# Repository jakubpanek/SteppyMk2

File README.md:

# Steppy Mk2

The goal of this project is to create a versatile robotic platform for robotic competitions.

It started with a very primitive PCB design that featured just a few, mostly through-hole components and evolved into a much more complicated design with over a hundred SMD components.

## Main features:
- NXP's FRDM dev boards, Arduino compatibility
- Two NEMA8 stepper motors
- Fits onto 100x100mm PCB for cheap manufacturing
- RGB LEDs
- OLED display
- Joystick
- Buzzer
- I²C battery voltage sensor
- Interchangeable sensor board

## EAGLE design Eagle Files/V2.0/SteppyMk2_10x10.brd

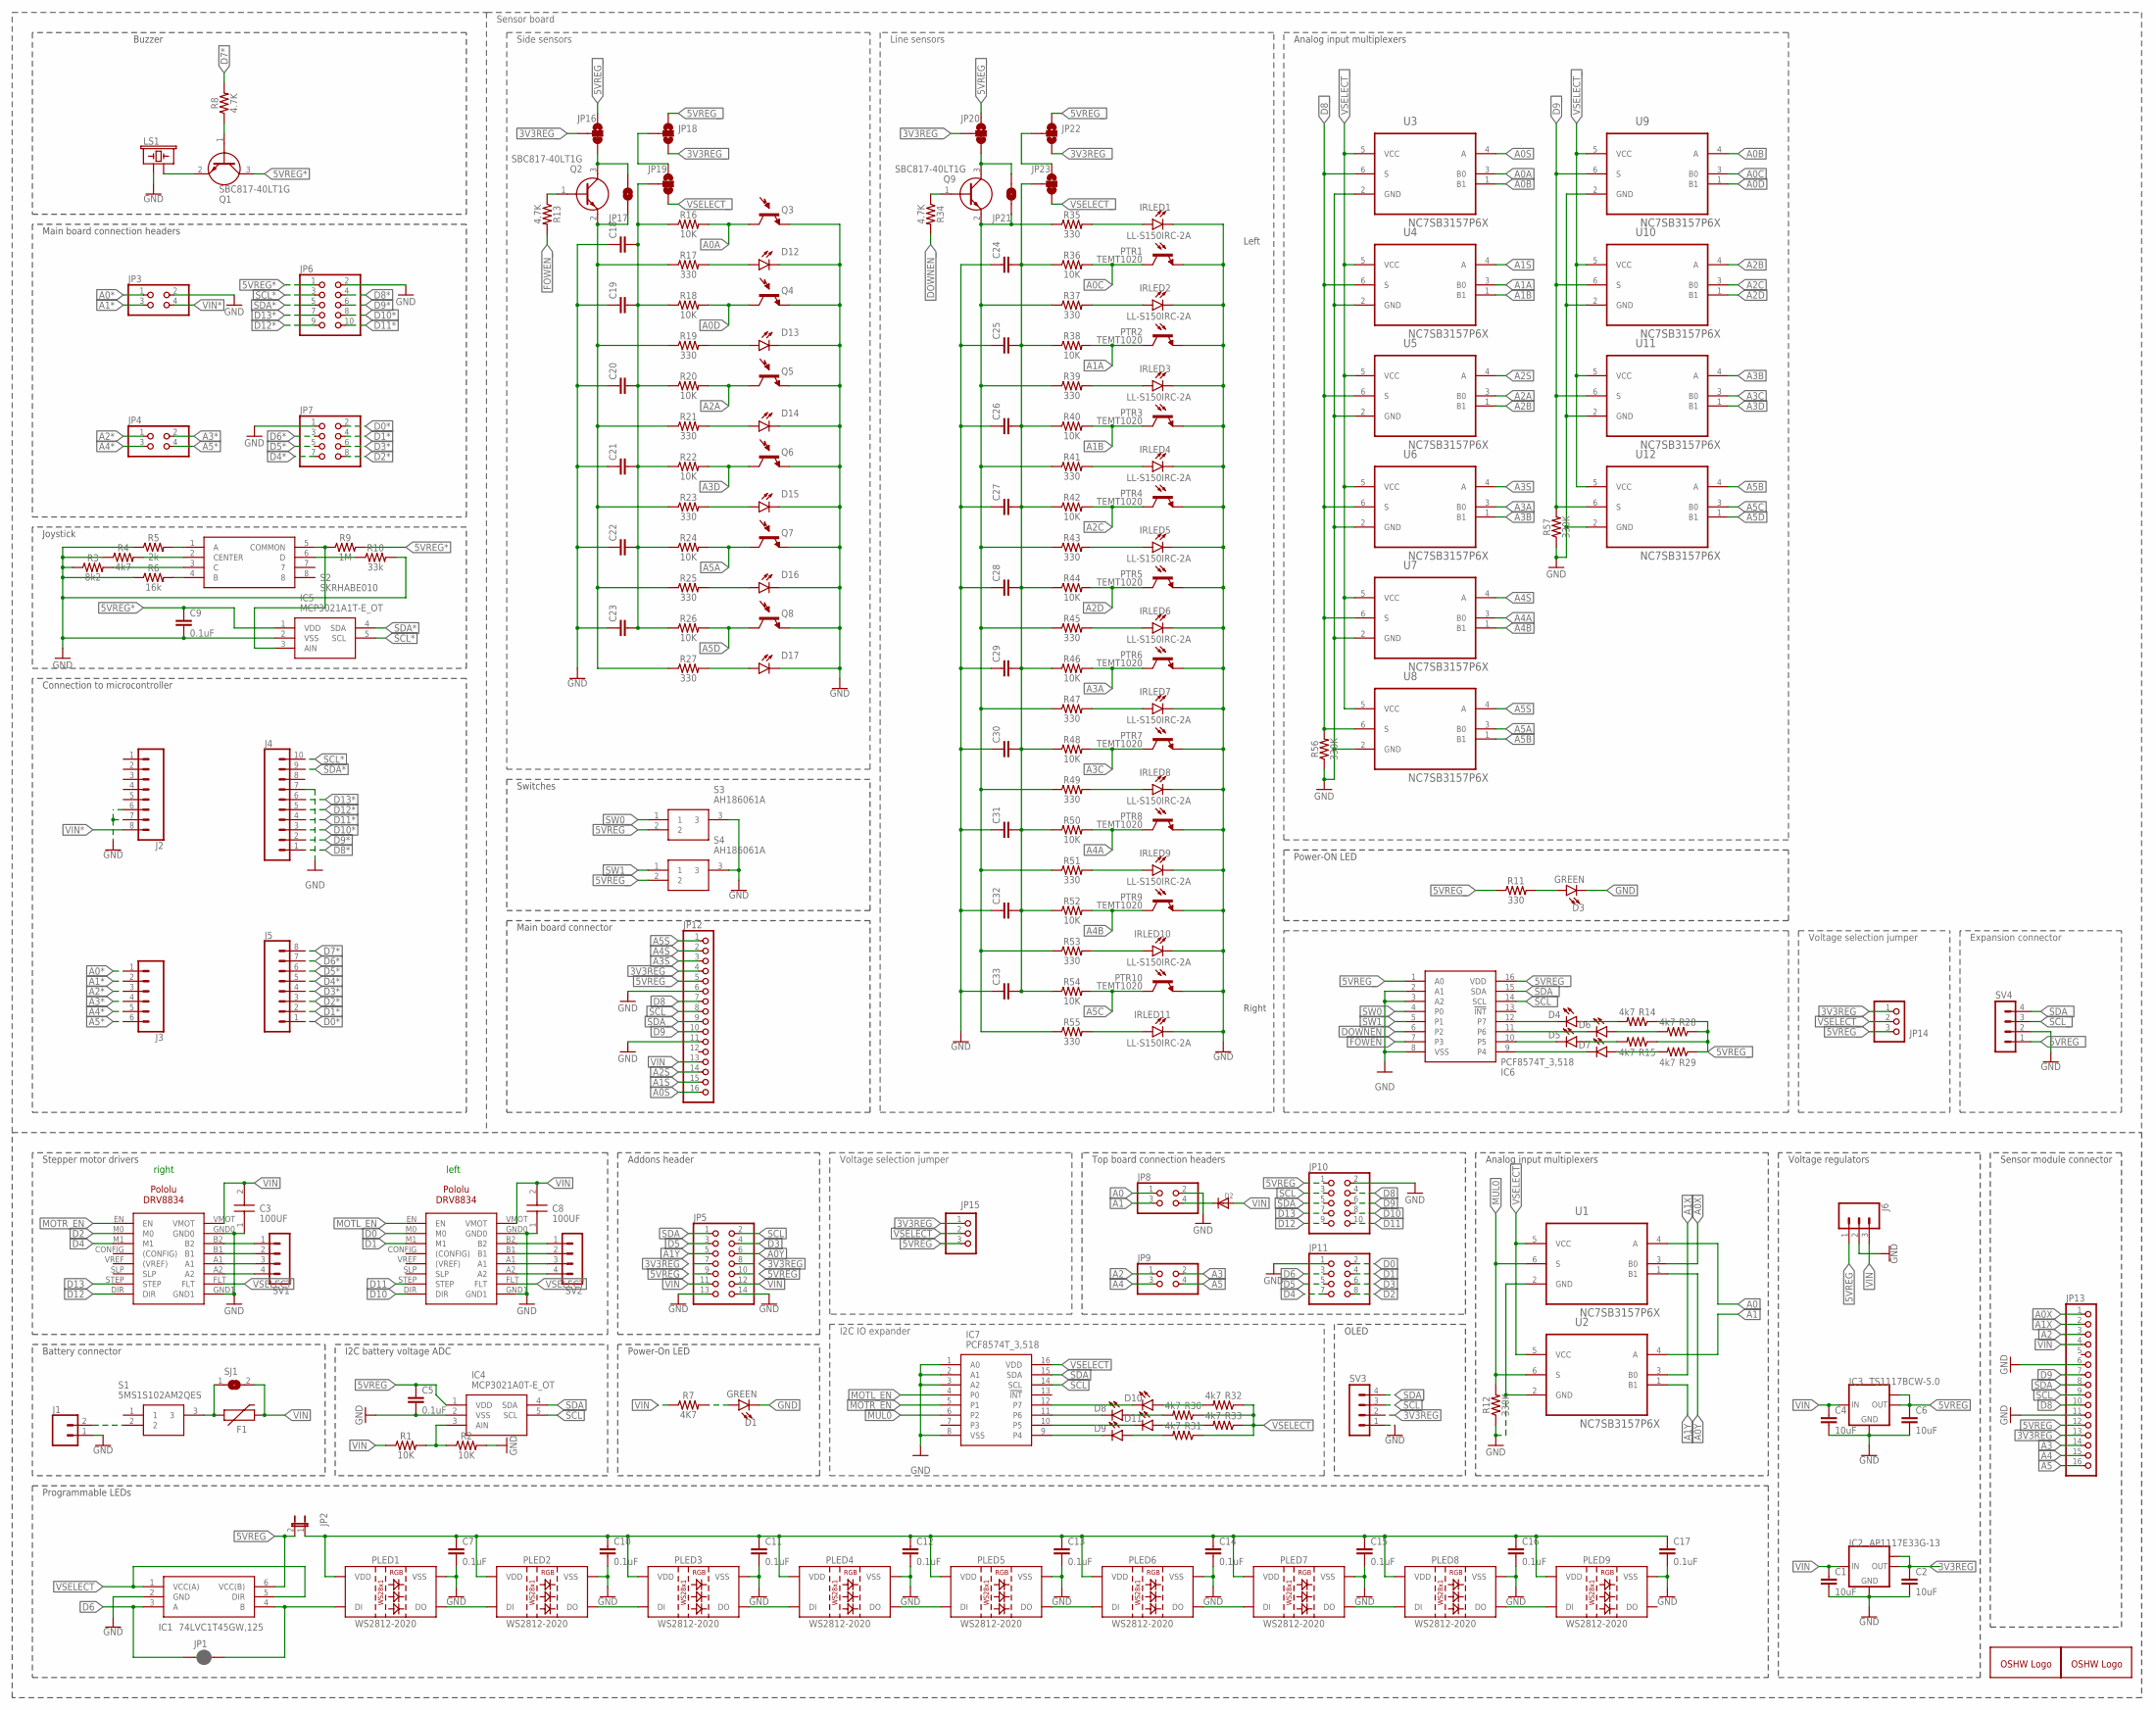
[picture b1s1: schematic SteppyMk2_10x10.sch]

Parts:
C1, C2, C4, C6: 10uF; 0805
C3, C8: 100UF; CAPM7058X610N
C5: 0.1uF; 0603
C7, C9, C10, C11, C12, C13, C14, C15, C16, C17: 0.1uF; C0805
C18, C19, C20, C21, C22, C23, C24, C25, C26, C27, C28, C29, C30, C31, C32, C33: C-EUC0805; C0805
D1, D3, D4, D5, D6, D7, D8, D9, D10, D11: GREEN; LED-1206
D2: DIODESMA; SMADIODE
D12, D13, D14, D15, D16, D17: LED-IRSIDE_EMITTER; LTE-302
DRV1, DRV2: POLOLU-DRV8825
F1: PPTC_PTH; PTH
GOLD_ORB_SM1: OSHWLOGOLOGO8MM; OSHW_8MM
GOLD_ORB_SM2: OSHWLOGOLOGO5MM; OSHW_5MM
IC1: 74LVC1T45GW,125; SOT65P210X110-6N
IC2: AP1117E33G-13; SOT223
IC3: TS1117BCW-5.0; SOT223
IC4: MCP3021A0T-E_OT; SOT95P280X145-5N
IC5: MCP3021A1T-E_OT; SOT95P280X145-5N
IC6, IC7: PCF8574T_3,518; SOIC127P1032X265-16N
IRLED1, IRLED2, IRLED3, IRLED4, IRLED5, IRLED6, IRLED7, IRLED8, IRLED9, IRLED10, IRLED11: LL-S150IRC-2A; LEDC3215X130N
J1: CONN_02; 1X02
J2, J5: CONN_08"; 1X08
J3: CONN_06SILK_FEMALE_PTH; 1X06
J4: CONN_10"; 1X10
J6: 455-1750-1-ND; 1X03
JP1: JUMPER-SMT_2_NC_PASTE_SILK; SMT-JUMPER_2_NC_PASTE_SILK
JP2: JP1E; JP1
JP3, JP4, JP8, JP9: PINHD-2X2; 2X02
JP5: PINHD-2X7; 2X07
JP6, JP10: PINHD-2X5; 2X05
JP7, JP11: PINHD-2X4; 2X04
JP12: PINHD-1X16/90; 1X16/90
JP13: PINHD-1X16; 1X16
JP14, JP15: PINHD-1X3; 1X03
JP16, JP19, JP20, JP23: JUMPER-SMT_3_1-NC_TRACE_NO-SILK; SMT-JUMPER_3_1-NC_TRACE_NO-SILK
JP17, JP21: JUMPER-SMT_2_NO_NO-SILK; SMT-JUMPER_2_NO_NO-SILK
JP18, JP22: JUMPER-SMT_3_NO_NO_SILK; SMT-JUMPER_3_0-NO_TRACE_NO-SILK
LS1: BUZZER-PTH_NO_SILK; BUZZER-12MM-NS
PLED1, PLED2, PLED3, PLED4, PLED5, PLED6, PLED7, PLED8, PLED9: WS2812-2020
PTR1, PTR2, PTR3, PTR4, PTR5, PTR6, PTR7, PTR8, PTR9, PTR10: TEMT1020
Q1, Q2, Q9: SBC817-40LT1G; SOT96P237X111-3N
Q3, Q4, Q5, Q6, Q7, Q8: LTR-301
R1, R2, R16, R18, R20, R22, R24, R26, R36, R38, R40, R42, R44, R46, R48, R50, R52, R54: 10K; 0805
R3: 8k2; 0805
R4, R14, R15, R28, R29, R30, R31, R32, R33: 4k7; 0805
R5: 2k; 0805
R6: 16k; 0805
R7: 4K7; 0805
R8, R13, R34: 4.7K; 0805
R9: 1M; 0805
R10: 33k; 0805
R11, R17, R19, R21, R23, R25, R27, R35, R37, R39, R41, R43, R45, R47, R49, R51, R53, R55: 330; 0805
R12, R56, R57: 330K; 0805
S1: 5MS1S102AM2QES
S2: SKRHABE010
S3, S4: AH186061A
SJ1: SJW
SV1, SV2, SV3, SV4: MA04-1
U1, U2, U3, U4, U5, U6, U7, U8, U9, U10, U11, U12: NC7SB3157P6X; SOT65P210X110-6N

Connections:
3V3REG: C2.1, IC2.2 (OUT), IC2.TAB (OUT1), JP5.7, JP5.8, JP13.13, JP15.1, SV3.2
3V3REG_: JP12.4, JP14.1, JP16.2, JP18.3, JP20.2, JP22.3
5VREG: C5.1, C6.1, IC1.6 (VCC(B)), IC3.2 (OUT), IC3.TAB (OUT1), IC4.1 (VDD), J6.1, JP2.2, JP5.9, JP5.10, JP10.1, JP13.12, JP15.3
5VREG*: C9.1, IC5.1 (VDD), JP6.1, Q1.3 (C), R9.2
5VREG_: IC6.1 (A0), IC6.16 (VDD), JP12.5, JP14.3, JP16.1, JP18.1, JP20.1, JP22.1, R11.1, R14.1, R15.1, R28.1, R29.1, S3.2, S4.2, SV4.1
A0: JP8.1, U1.4 (A)
A0*: J3.1, JP3.1
A0A: Q3.C (C1), R16.2, U3.3 (B0)
A0B: U3.1 (B1), U9.4 (A)
A0C: PTR1.1 (C), R36.2, U9.3 (B0)
A0D: Q4.C (C1), R18.2, U9.1 (B1)
A0S: JP12.16, U3.4 (A)
A0X: JP13.1, U1.3 (B0)
A0Y: JP5.6, U1.1 (B1)
A1: JP8.3, U2.4 (A)
A1*: J3.2, JP3.3
A1A: PTR2.1 (C), R38.2, U4.3 (B0)
A1B: PTR3.1 (C), R40.2, U4.1 (B1)
A1S: JP12.15, U4.4 (A)
A1X: JP13.2, U2.3 (B0)
A1Y: JP5.5, U2.1 (B1)
A2: JP9.1, JP13.3
A2*: J3.3, JP4.1
A2A: Q5.C (C1), R20.2, U5.3 (B0)
A2B: U5.1 (B1), U10.4 (A)
A2C: PTR4.1 (C), R42.2, U10.3 (B0)
A2D: PTR5.1 (C), R44.2, U10.1 (B1)
A2S: JP12.14, U5.4 (A)
A3: JP9.2, JP13.14
A3*: J3.4, JP4.2
A3A: PTR6.1 (C), R46.2, U6.3 (B0)
A3B: U6.1 (B1), U11.4 (A)
A3C: PTR7.1 (C), R48.2, U11.3 (B0)
A3D: Q6.C (C1), R22.2, U11.1 (B1)
A3S: JP12.3, U6.4 (A)
A4: JP9.3, JP13.15
A4*: J3.5, JP4.3
A4A: PTR8.1 (C), R50.2, U7.3 (B0)
A4B: PTR9.1 (C), R52.2, U7.1 (B1)
A4S: JP12.2, U7.4 (A)
A5: JP9.4, JP13.16
A5*: J3.6, JP4.4
A5A: Q7.C (C1), R24.2, U8.3 (B0)
A5B: U8.1 (B1), U12.4 (A)
A5C: PTR10.1 (C), R54.2, U12.3 (B0)
A5D: Q8.C (C1), R26.2, U12.1 (B1)
A5S: JP12.1, U8.4 (A)
D0: DRV2.M0, JP11.2
D0*: J5.1, JP7.2
D1: DRV2.M1, JP11.4
D1*: J5.2, JP7.4
D2: DRV1.M0, JP11.8
D2*: J5.3, JP7.8
D3: JP5.4, JP11.6
D3*: J5.4, JP7.6
D4: DRV1.M1, JP11.7
D4*: J5.5, JP7.7
D5: JP5.3, JP11.5
D5*: J5.6, JP7.5
D6: IC1.3 (A), JP1.1, JP11.3
D6*: J5.7, JP7.3
D7*: J5.8, R8.2
D8: JP10.4, JP13.10
D8*: J4.1, JP6.4
D8_: JP12.7, R56.2, U3.6 (S), U4.6 (S), U5.6 (S), U6.6 (S), U7.6 (S), U8.6 (S)
D9: JP10.6, JP13.7
D9*: J4.2, JP6.6
D9_: JP12.10, R57.2, U9.6 (S), U10.6 (S), U11.6 (S), U12.6 (S)
D10: DRV2.DIR, JP10.8
D10*: J4.3, JP6.8
D11: DRV2.STEP, JP10.10
D11*: J4.4, JP6.10
D12: DRV1.DIR, JP10.9
D12*: J4.5, JP6.9
D13: DRV1.STEP, JP10.7
D13*: J4.6, JP6.7
DOWNEN_: IC6.6 (P2), R34.2
FOWEN_: IC6.7 (P3), R13.2
GND: C1.2, C2.2, C3.1, C4.2, C5.2, C6.2, C7.2, C8.1, C9.2, C10.2, C11.2, C12.2, C13.2, C14.2, C15.2, C16.2, C17.2, C18.1, C19.1, C20.1, C21.1, C22.1, C23.1, C24.1, C25.1, C26.1, C27.1, C28.1, C29.1, C30.1, C31.1, C32.1, C33.1, D1.C, D3.C, D12.C, D13.C, D14.C, D15.C, D16.C, D17.C, DRV1.GND0, DRV1.GND1, DRV2.GND0, DRV2.GND1, IC1.2 (GND), IC2.1 (GND), IC3.1 (GND), IC4.2 (VSS), IC5.2 (VSS), IC6.2 (A1), IC6.3 (A2), IC6.8 (VSS), IC7.1 (A0), IC7.2 (A1), IC7.3 (A2), IC7.8 (VSS), IRLED1.2 (C), IRLED2.2 (C), IRLED3.2 (C), IRLED4.2 (C), IRLED5.2 (C), IRLED6.2 (C), IRLED7.2 (C), IRLED8.2 (C), IRLED9.2 (C), IRLED10.2 (C), IRLED11.2 (C), J1.1, J2.6, J2.7, J4.7, J6.2, JP3.2, JP5.13, JP5.14, JP6.2, JP7.1, JP8.2, JP10.2, JP11.1, JP12.6, JP12.11, JP13.6, JP13.11, LS1.+ (1), PLED1.2 (VSS), PLED2.2 (VSS), PLED3.2 (VSS), PLED4.2 (VSS), PLED5.2 (VSS), PLED6.2 (VSS), PLED7.2 (VSS), PLED8.2 (VSS), PLED9.2 (VSS), PTR1.2 (E), PTR2.2 (E), PTR3.2 (E), PTR4.2 (E), PTR5.2 (E), PTR6.2 (E), PTR7.2 (E), PTR8.2 (E), PTR9.2 (E), PTR10.2 (E), Q3.E (E1), Q4.E (E1), Q5.E (E1), Q6.E (E1), Q7.E (E1), Q8.E (E1), R2.2, R3.1, R4.1, R5.1, R6.1, R10.2, R12.1, R56.1, R57.1, S3.3, S4.3, SV3.1, SV4.2, U1.2 (GND), U2.2 (GND), U3.2 (GND), U4.2 (GND), U5.2 (GND), U6.2 (GND), U7.2 (GND), U8.2 (GND), U9.2 (GND), U10.2 (GND), U11.2 (GND), U12.2 (GND)
GND1: D6.C, IC6.11 (P6)
GND2: D5.C, IC6.10 (P5)
GND3: D7.C, IC6.9 (P4)
MOTL_EN: DRV2.EN, IC7.4 (P0)
MOTR_EN: DRV1.EN, IC7.5 (P1)
MUL0: IC7.6 (P2), R12.2, U1.6 (S), U2.6 (S)
unnamed: IRLED9.1 (A), R51.2
unnamed: IRLED2.1 (A), R37.2
unnamed: D4.A, R14.2
unnamed: D2.C, JP8.4
unnamed: Q2.1 (B), R13.1
unnamed: IRLED1.1 (A), R35.2
unnamed: IC1.4 (B), JP1.2, PLED1.3 (DI)
unnamed: D8.A, R30.2
unnamed: D11.C, IC7.10 (P5)
unnamed: D9.A, R31.2
unnamed: PLED6.1 (DO), PLED7.3 (DI)
unnamed: IRLED3.1 (A), R39.2
unnamed: PLED7.1 (DO), PLED8.3 (DI)
unnamed: PLED8.1 (DO), PLED9.3 (DI)
unnamed: D1.A, R7.2
unnamed: DRV2.B2, SV2.1
unnamed: DRV2.B1, SV2.2
unnamed: DRV2.A1, SV2.3
unnamed: DRV2.A2, SV2.4
unnamed: D6.A, R28.2
unnamed: R6.2, S2.4 (B)
unnamed: D3.A, R11.2
unnamed: IRLED4.1 (A), R41.2
unnamed: D5.A, R15.2
unnamed: R3.2, S2.3 (C)
unnamed: DRV1.B2, SV1.1
unnamed: DRV1.B1, SV1.2
unnamed: DRV1.A1, SV1.3
unnamed: DRV1.A2, SV1.4
unnamed: J1.2, S1.2
unnamed: R4.2, S2.2 (CENTER)
unnamed: LS1.- (2), Q1.2 (E)
unnamed: Q1.1 (B), R8.1
unnamed: IC4.3 (AIN), R1.2, R2.1
unnamed: R5.2, S2.1 (A)
unnamed: D10.C, IC7.12 (P7)
unnamed: IC5.3 (AIN), R9.1, S2.5 (COMMON)
unnamed: R10.1, S2.6 (D)
unnamed: D8.C, IC7.11 (P6)
unnamed: D7.A, R29.2
unnamed: D9.C, IC7.9 (P4)
unnamed: D11.A, R33.2
unnamed: D10.A, R32.2
unnamed: C7.1, C10.1, C11.1, C12.1, C13.1, C14.1, C15.1, C16.1, C17.1, JP2.1, PLED1.4 (VDD), PLED2.4 (VDD), PLED3.4 (VDD), PLED4.4 (VDD), PLED5.4 (VDD), PLED6.4 (VDD), PLED7.4 (VDD), PLED8.4 (VDD), PLED9.4 (VDD)
unnamed: IRLED5.1 (A), R43.2
unnamed: PLED2.1 (DO), PLED3.3 (DI)
unnamed: PLED3.1 (DO), PLED4.3 (DI)
unnamed: IRLED6.1 (A), R45.2
unnamed: PLED4.1 (DO), PLED5.3 (DI)
unnamed: IRLED7.1 (A), R47.2
unnamed: PLED5.1 (DO), PLED6.3 (DI)
unnamed: JP16.3, JP17.2, Q2.3 (C)
unnamed: IRLED8.1 (A), R49.2
unnamed: JP18.2, JP19.1
unnamed: PLED1.1 (DO), PLED2.3 (DI)
unnamed: JP22.2, JP23.1
unnamed: JP20.3, JP21.2, Q9.3 (C)
unnamed: D4.C, IC6.12 (P7)
unnamed: IRLED10.1 (A), R53.2
unnamed: IRLED11.1 (A), R55.2
unnamed: D12.A, R17.2
unnamed: D13.A, R19.2
unnamed: Q9.1 (B), R34.1
unnamed: D14.A, R21.2
unnamed: F1.P$1 (1), S1.3, SJ1.1
unnamed: D15.A, R23.2
unnamed: JP21.1, Q9.2 (E), R35.1, R37.1, R39.1, R41.1, R43.1, R45.1, R47.1, R49.1, R51.1, R53.1, R55.1
unnamed: D16.A, R25.2
unnamed: D17.A, R27.2
unnamed: JP17.1, Q2.2 (E), R17.1, R19.1, R21.1, R23.1, R25.1, R27.1
NE9878: C24.2, C25.2, C26.2, C27.2, C28.2, C29.2, C30.2, C31.2, C32.2, C33.2, JP23.2, R36.1, R38.1, R40.1, R42.1, R44.1, R46.1, R48.1, R50.1, R52.1, R54.1
NET56SDFSF: C18.2, C19.2, C20.2, C21.2, C22.2, C23.2, JP19.2, R16.1, R18.1, R20.1, R22.1, R24.1, R26.1
SCL: IC4.5 (SCL), IC7.14 (SCL), JP5.2, JP10.3, JP13.9, SV3.3
SCL*: IC5.5 (SCL), J4.10, JP6.3
SCL_: IC6.14 (SCL), JP12.8, SV4.3
SDA: IC4.4 (SDA), IC7.15 (SDA), JP5.1, JP10.5, JP13.8, SV3.4
SDA*: IC5.4 (SDA), J4.9, JP6.5
SDA_: IC6.15 (SDA), JP12.9, SV4.4
SW0_: IC6.4 (P0), S3.1
SW1_: IC6.5 (P1), S4.1
VIN: C1.1, C3.2, C4.1, C8.2, D2.A, DRV1.VMOT, DRV2.VMOT, F1.P$2 (2), IC2.3 (IN), IC3.3 (IN), J6.3, JP5.11, JP5.12, JP13.4, R1.1, R7.1, SJ1.2
VIN*: J2.8, JP3.4
VIN_: JP12.13
VSELECT: DRV1.FLT, DRV2.FLT, IC1.1 (VCC(A)), IC1.5 (DIR), IC7.16 (VDD), JP15.2, R30.1, R31.1, R32.1, R33.1, U1.5 (VCC), U2.5 (VCC)
VSELECT_: JP14.2, JP19.3, JP23.3, U3.5 (VCC), U4.5 (VCC), U5.5 (VCC), U6.5 (VCC), U7.5 (VCC), U8.5 (VCC), U9.5 (VCC), U10.5 (VCC), U11.5 (VCC), U12.5 (VCC)

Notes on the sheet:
Battery connector
I2C battery voltage ADC
Programmable LEDs
Stepper motor drivers
Voltage regulators
Buzzer
Joystick
Right
Left
Addons header
OLED
Connection to microcontroller
Main board connection headers
Top board connection headers
Sensor module connector
Main board connector
Power-ON LED
Power-On LED
Switches
Analog input multiplexers
left
right
Voltage selection jumper
I2C IO expander
Expansion connector
Sensor board
Line sensors
Side sensors

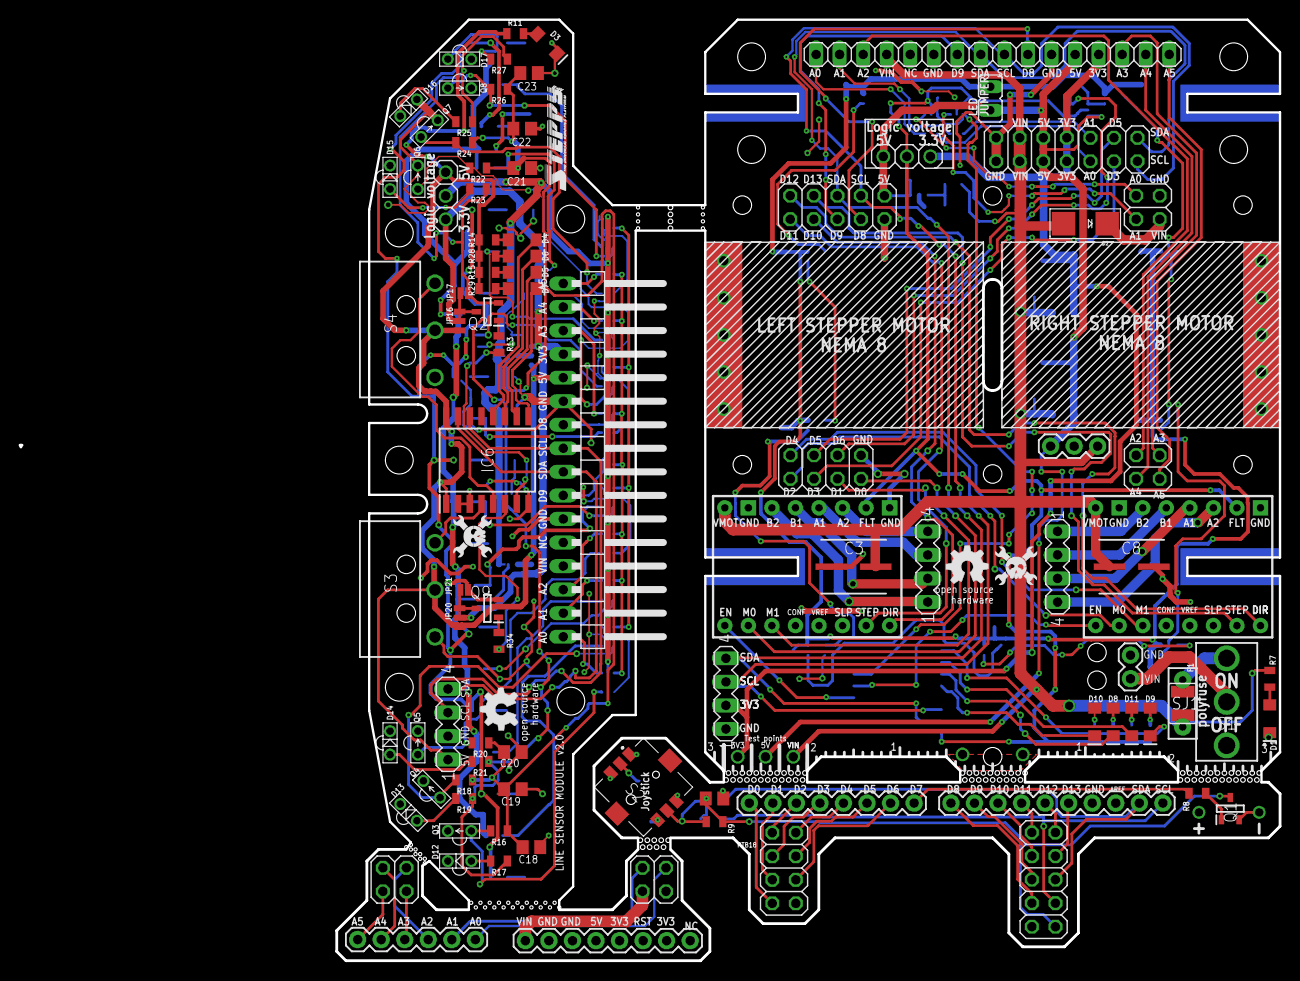
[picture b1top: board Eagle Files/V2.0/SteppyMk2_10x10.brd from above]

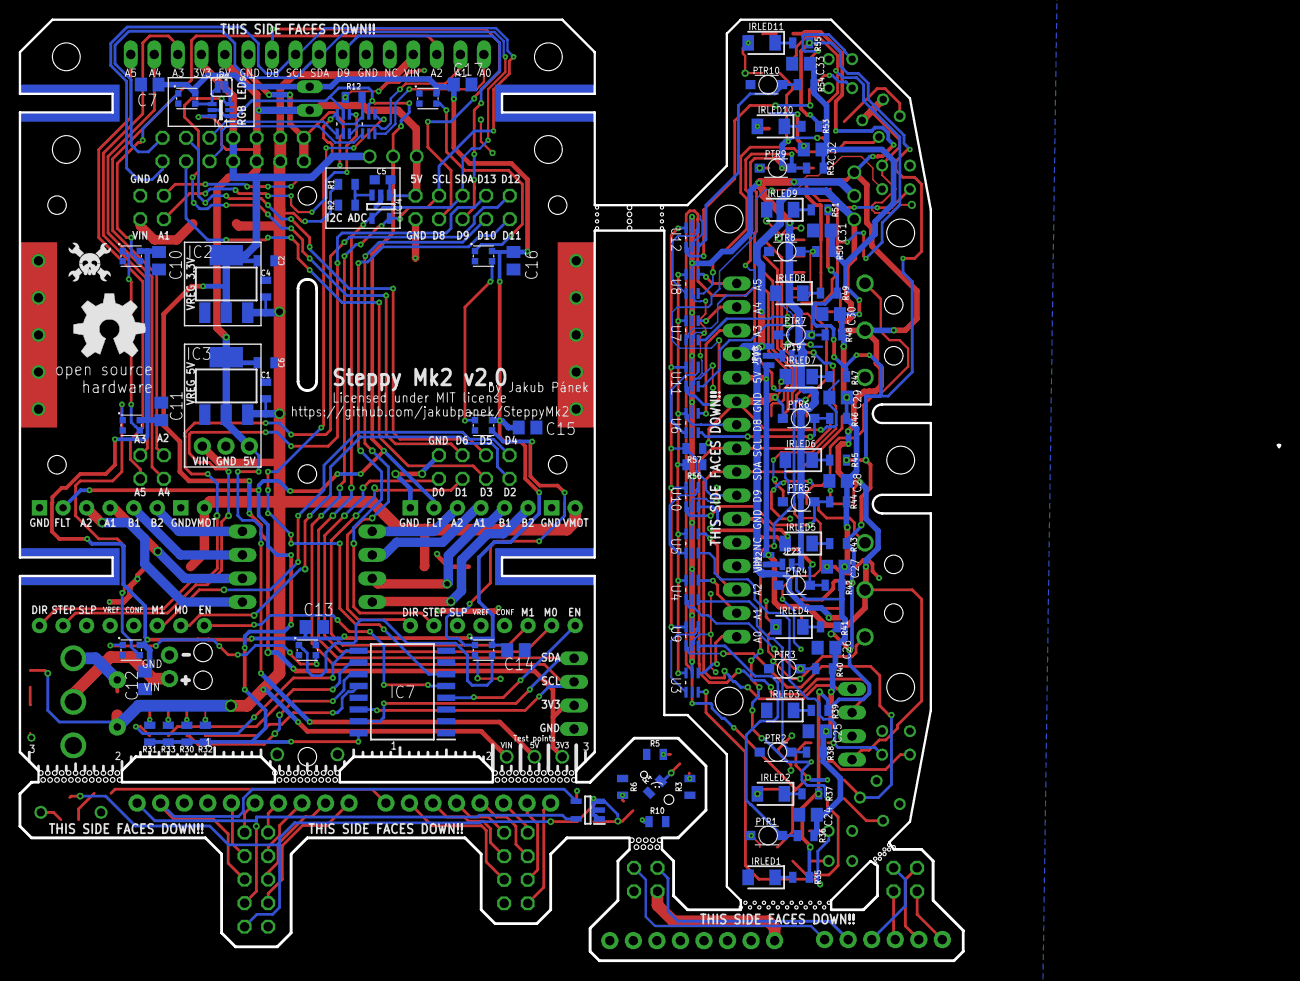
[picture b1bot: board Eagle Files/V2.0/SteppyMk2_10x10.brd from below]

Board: 2 copper layers, 101.8 x 101.5 mm, 210 parts (113 on the bottom side), 169 nets.

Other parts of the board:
GOLD_ORB_SM3: OSHWLOGOLOGO5MM; OSHW_5MM

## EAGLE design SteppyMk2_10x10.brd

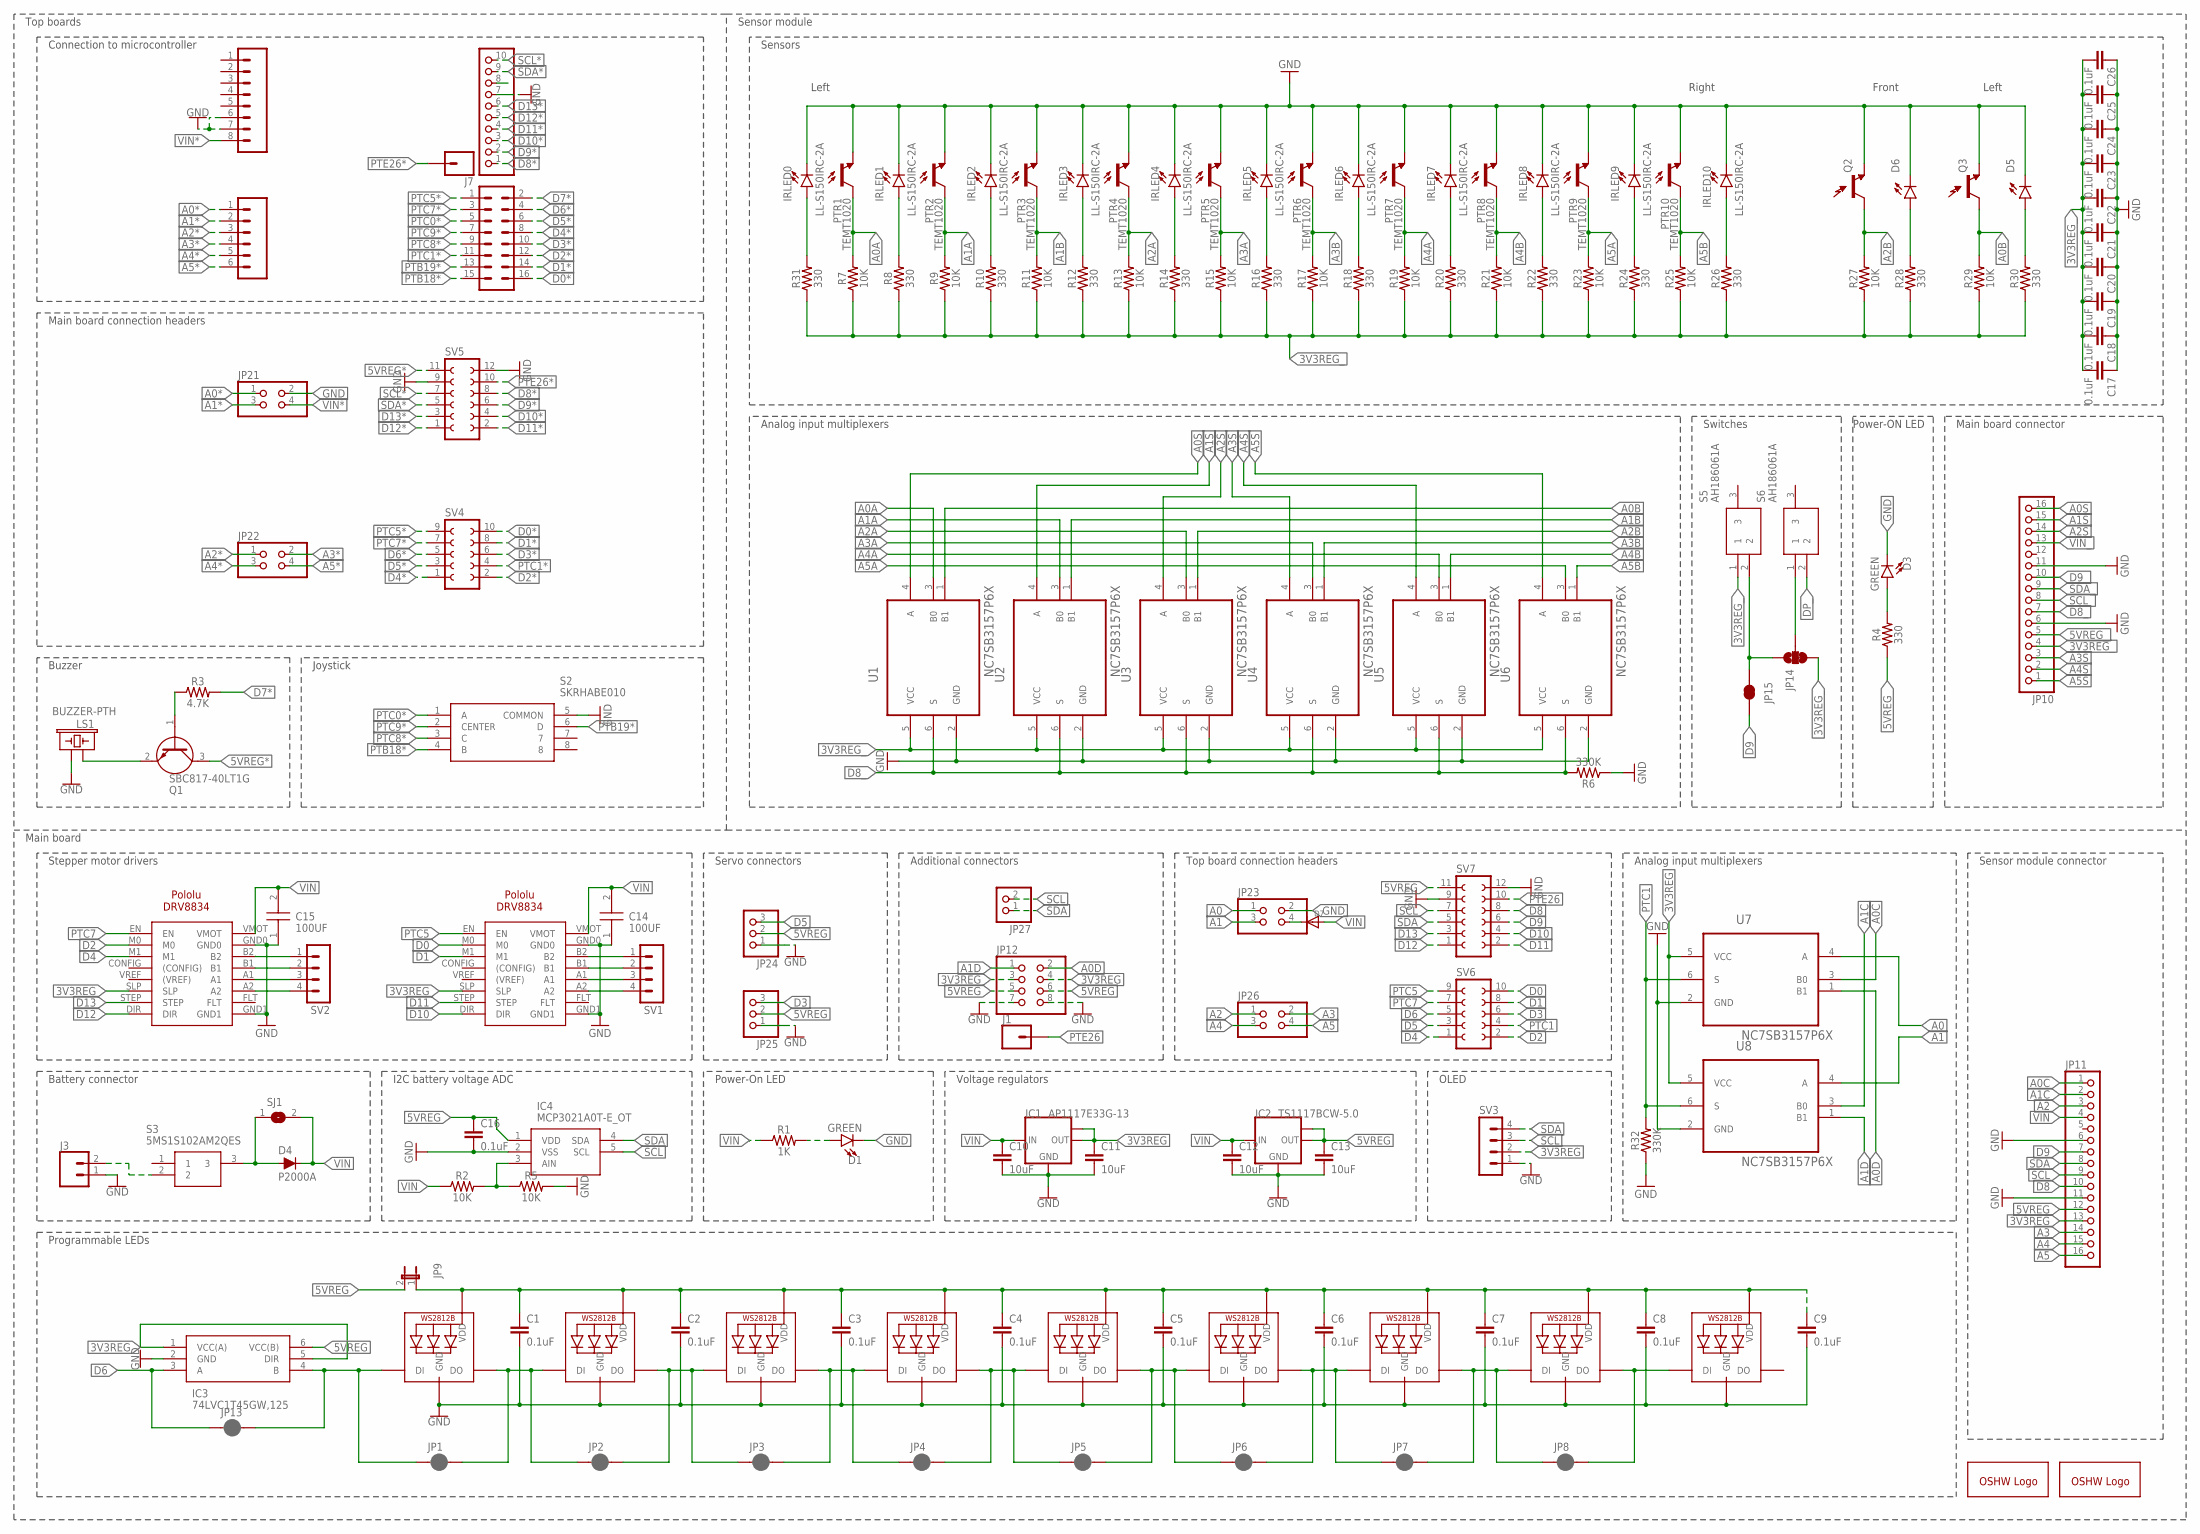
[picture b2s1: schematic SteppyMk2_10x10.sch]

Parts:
C1, C2, C3, C4, C5, C6, C7, C8, C9, C16, C17, C18, C19, C20, C21, C22, C23, C24, C25, C26: 0.1uF; 0603
C10, C11, C12, C13: 10uF; 0805
C14, C15: 100UF; CAPM7058X610N
CONLEFT: POLOLU-DRV8825
D1, D3: GREEN; LED-1206
D4: P2000A; DIODE-1N4001
D5, D6: LED-IRSIDE_EMITTER; LTE-302
D7: DIODESMA; SMADIODE
GOLD_ORB_SM1: OSHWLOGOLOGO8MM; OSHW_8MM
GOLD_ORB_SM2: OSHWLOGOLOGO5MM; OSHW_5MM
IC1: AP1117E33G-13; SOT223
IC2: TS1117BCW-5.0; SOT223
IC3: 74LVC1T45GW,125; SOT65P210X110-6N
IC4: MCP3021A0T-E_OT; SOT95P280X145-5N
IRLED0, IRLED1, IRLED2, IRLED3, IRLED4, IRLED5, IRLED6, IRLED7, IRLED8, IRLED9, IRLED10: LL-S150IRC-2A; LEDC3215X130N
J1, J7: CONN_01; 1X01
J3: CONN_02; 1X02
J5: CONN_08"; 1X08
J6: CONN_06SILK_FEMALE_PTH; 1X06
J8: CONN_08X2_HEADER; 2X8
JP1, JP2, JP3, JP4, JP5, JP6, JP7, JP8, JP13: JUMPER-SMT_2_NC_PASTE_SILK; SMT-JUMPER_2_NC_PASTE_SILK
JP9: JP1E; JP1
JP10: PINHD-1X16/90; 1X16/90
JP11: PINHD-1X16; 1X16
JP12: PINHD-2X4; 2X04
JP14: JUMPER-SMT_3_1-NC_TRACE_SILK; SMT-JUMPER_3_1-NC_TRACE_SILK
JP15: JUMPER-SMT_2_NC_TRACE_SILK; SMT-JUMPER_2_NC_TRACE_SILK
JP21, JP22, JP23, JP26: PINHD-2X2; 2X02
JP24, JP25: PINHD-1X3; 1X03
JP27: PINHD-1X2; 1X02
LED1, LED2, LED3, LED4, LED5, LED6, LED7, LED8, LED9: WS2812B3535; LED3535
LS1: BUZZER-PTH; BUZZER-12MM
PTR1, PTR2, PTR3, PTR4, PTR5, PTR6, PTR7, PTR8, PTR9, PTR10: TEMT1020
Q1: SBC817-40LT1G; SOT96P237X111-3N
Q2, Q3: LTR-301
R1: 1K; 0805
R2, R5, R7, R9, R11, R13, R15, R17, R19, R21, R23, R25, R27, R29: 10K; 0805
R3: 4.7K; 0805
R4, R8, R10, R12, R14, R16, R18, R20, R22, R24, R26, R28, R30, R31: 330; 0805
R6, R32: 330K; 0805
S2: SKRHABE010
S3: 5MS1S102AM2QES
S5, S6: AH186061A
SJ1: SJW
SV1, SV2, SV3: MA04-1
SV4, SV6: FE05-2
SV5, SV7: FE06-2
U1, U2, U3, U4, U5, U6, U7, U8: NC7SB3157P6X; SOT65P210X110-6N
U$1: PINHD-1X10; 1X10-BIG
U$2: POLOLU-DRV8825

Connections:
3V3REG: C11.1, CONLEFT.SLP, IC1.2 (OUT), IC1.TAB (OUT1), IC3.1 (VCC(A)), IC3.5 (DIR), JP11.13, JP12.3, JP12.4, SV3.2, U7.5 (VCC), U8.5 (VCC), U$2.SLP
3V3REG_: C17.2, C18.2, C19.2, C20.2, C21.2, C22.2, C23.2, C24.2, C25.2, C26.2, JP10.4, JP14.3, R7.1, R8.1, R9.1, R10.1, R11.1, R12.1, R13.1, R14.1, R15.1, R16.1, R17.1, R18.1, R19.1, R20.1, R21.1, R22.1, R23.1, R24.1, R25.1, R26.1, R27.1, R28.1, R29.1, R30.1, R31.1, S5.1, U1.5 (VCC), U2.5 (VCC), U3.5 (VCC), U4.5 (VCC), U5.5 (VCC), U6.5 (VCC)
5VREG: C13.1, C16.1, IC2.2 (OUT), IC2.TAB (OUT1), IC3.6 (VCC(B)), IC4.1 (VDD), JP9.2, JP11.12, JP12.5, JP12.6, JP24.2, JP25.2, SV7.11
5VREG*: Q1.3 (C), SV5.11
5VREG_: JP10.5, R4.1
A0: JP23.1, U7.4 (A)
A0*: J6.1, JP21.1
A0A: PTR1.1 (C), R7.2, U1.3 (B0)
A0B: Q3.C (C1), R29.2, U1.1 (B1)
A0C: JP11.1, U7.3 (B0)
A0D: JP12.2, U7.1 (B1)
A0S: JP10.16, U1.4 (A)
A1: JP23.3, U8.4 (A)
A1*: J6.2, JP21.3
A1A: PTR2.1 (C), R9.2, U2.3 (B0)
A1B: PTR3.1 (C), R11.2, U2.1 (B1)
A1C: JP11.2, U8.3 (B0)
A1D: JP12.1, U8.1 (B1)
A1S: JP10.15, U2.4 (A)
A2: JP11.3, JP26.1
A2*: J6.3, JP22.1
A2A: PTR4.1 (C), R13.2, U3.3 (B0)
A2B: Q2.C (C1), R27.2, U3.1 (B1)
A2S: JP10.14, U3.4 (A)
A3: JP11.14, JP26.2
A3*: J6.4, JP22.2
A3A: PTR5.1 (C), R15.2, U4.3 (B0)
A3B: PTR6.1 (C), R17.2, U4.1 (B1)
A3S: JP10.3, U4.4 (A)
A4: JP11.15, JP26.3
A4*: J6.5, JP22.3
A4A: PTR7.1 (C), R19.2, U5.3 (B0)
A4B: PTR8.1 (C), R21.2, U5.1 (B1)
A4S: JP10.2, U5.4 (A)
A5: JP11.16, JP26.4
A5*: J6.6, JP22.4
A5A: PTR9.1 (C), R23.2, U6.3 (B0)
A5B: PTR10.1 (C), R25.2, U6.1 (B1)
A5S: JP10.1, U6.4 (A)
D0: SV6.10, U$2.M0
D0*: J8.16, SV4.10
D1: SV6.8, U$2.M1
D1*: J8.14, SV4.8
D2: CONLEFT.M0, SV6.2
D2*: J8.12, SV4.2
D3: JP25.3, SV6.6
D3*: J8.10, SV4.6
D4: CONLEFT.M1, SV6.1
D4*: J8.8, SV4.1
D5: JP24.3, SV6.3
D5*: J8.6, SV4.3
D6: IC3.3 (A), JP13.1, SV6.5
D6*: J8.4, SV4.5
D7*: J8.2, R3.2
D8: JP11.10, SV7.8
D8*: SV5.8, U$1.1
D8_: JP10.7, R6.2, U1.6 (S), U2.6 (S), U3.6 (S), U4.6 (S), U5.6 (S), U6.6 (S)
D9: JP11.7, SV7.6
D9*: SV5.6, U$1.2
D9_: JP10.10, JP15.1
D10: SV7.4, U$2.DIR
D10*: SV5.4, U$1.3
D11: SV7.2, U$2.STEP
D11*: SV5.2, U$1.4
D12: CONLEFT.DIR, SV7.1
D12*: SV5.1, U$1.5
D13: CONLEFT.STEP, SV7.3
D13*: SV5.3, U$1.6
DP_: S6.2
GND: C1.2, C2.2, C3.2, C4.2, C5.2, C6.2, C7.2, C8.2, C9.2, C10.2, C11.2, C12.2, C13.2, C14.1, C15.1, C16.2, C17.1, C18.1, C19.1, C20.1, C21.1, C22.1, C23.1, C24.1, C25.1, C26.1, CONLEFT.GND0, CONLEFT.GND1, D1.C, D3.C, D5.C, D6.C, IC1.1 (GND), IC2.1 (GND), IC3.2 (GND), IC4.2 (VSS), IRLED0.2 (C), IRLED1.2 (C), IRLED2.2 (C), IRLED3.2 (C), IRLED4.2 (C), IRLED5.2 (C), IRLED6.2 (C), IRLED7.2 (C), IRLED8.2 (C), IRLED9.2 (C), IRLED10.2 (C), J3.1, J5.6, J5.7, JP10.6, JP10.11, JP11.6, JP11.11, JP12.7, JP12.8, JP21.2, JP23.2, JP24.1, JP25.1, LED1.4 (GND), LED2.4 (GND), LED3.4 (GND), LED4.4 (GND), LED5.4 (GND), LED6.4 (GND), LED7.4 (GND), LED8.4 (GND), LED9.4 (GND), LS1.- (2), PTR1.2 (E), PTR2.2 (E), PTR3.2 (E), PTR4.2 (E), PTR5.2 (E), PTR6.2 (E), PTR7.2 (E), PTR8.2 (E), PTR9.2 (E), PTR10.2 (E), Q2.E (E1), Q3.E (E1), R5.2, R6.1, R32.1, S2.5 (COMMON), SV3.1, SV5.9, SV5.12, SV7.9, SV7.12, U1.2 (GND), U2.2 (GND), U3.2 (GND), U4.2 (GND), U5.2 (GND), U6.2 (GND), U7.2 (GND), U8.2 (GND), U$1.7, U$2.GND0, U$2.GND1
unnamed: IRLED8.1 (A), R22.2
unnamed: IRLED1.1 (A), R8.2
unnamed: D6.A, R28.2
unnamed: D7.C, JP23.4
unnamed: JP14.2, S6.1
unnamed: IRLED0.1 (A), R31.2
unnamed: IC3.4 (B), JP1.1, JP13.2, LED1.1 (DI)
unnamed: JP2.2, JP3.1, LED2.3 (DO), LED3.1 (DI)
unnamed: JP3.2, JP4.1, LED3.3 (DO), LED4.1 (DI)
unnamed: JP4.2, JP5.1, LED4.3 (DO), LED5.1 (DI)
unnamed: JP5.2, JP6.1, LED5.3 (DO), LED6.1 (DI)
unnamed: JP6.2, JP7.1, LED6.3 (DO), LED7.1 (DI)
unnamed: IRLED2.1 (A), R10.2
unnamed: JP7.2, JP8.1, LED7.3 (DO), LED8.1 (DI)
unnamed: JP8.2, LED8.3 (DO), LED9.1 (DI)
unnamed: D1.A, R1.2
unnamed: SV1.1, U$2.B2
unnamed: SV1.2, U$2.B1
unnamed: SV1.3, U$2.A1
unnamed: SV1.4, U$2.A2
unnamed: D5.A, R30.2
unnamed: D3.A, R4.2
unnamed: IRLED3.1 (A), R12.2
unnamed: CONLEFT.B2, SV2.1
unnamed: CONLEFT.B1, SV2.2
unnamed: CONLEFT.A1, SV2.3
unnamed: CONLEFT.A2, SV2.4
unnamed: J3.2, S3.2
unnamed: LS1.+ (1), Q1.2 (E)
unnamed: Q1.1 (B), R3.1
unnamed: IC4.3 (AIN), R2.2, R5.1
unnamed: C1.1, C2.1, C3.1, C4.1, C5.1, C6.1, C7.1, C8.1, C9.1, JP9.1, LED1.2 (VDD), LED2.2 (VDD), LED3.2 (VDD), LED4.2 (VDD), LED5.2 (VDD), LED6.2 (VDD), LED7.2 (VDD), LED8.2 (VDD), LED9.2 (VDD)
unnamed: IRLED4.1 (A), R14.2
unnamed: IRLED5.1 (A), R16.2
unnamed: IRLED6.1 (A), R18.2
unnamed: IRLED7.1 (A), R20.2
unnamed: IRLED9.1 (A), R24.2
unnamed: JP14.1, JP15.2, S5.2
unnamed: IRLED10.1 (A), R26.2
unnamed: JP1.2, JP2.1, LED1.3 (DO), LED2.1 (DI)
unnamed: D4.A, S3.3, SJ1.1
PTB18*: J8.15, S2.4 (B)
PTB19*: J8.13, S2.6 (D)
PTC0*: J8.5, S2.1 (A)
PTC1: R32.2, SV6.4, U7.6 (S), U8.6 (S)
PTC1*: J8.11, SV4.4
PTC5: SV6.9, U$2.EN
PTC5*: J8.1, SV4.9
PTC7: CONLEFT.EN, SV6.7
PTC7*: J8.3, SV4.7
PTC8*: J8.9, S2.3 (C)
PTC9*: J8.7, S2.2 (CENTER)
PTE26: J1.1, SV7.10
PTE26*: J7.1, SV5.10
SCL: IC4.5 (SCL), JP11.9, JP27.2, SV3.3, SV7.7
SCL*: SV5.7, U$1.10
SCL_: JP10.8
SDA: IC4.4 (SDA), JP11.8, JP27.1, SV3.4, SV7.5
SDA*: SV5.5, U$1.9
SDA_: JP10.9
VIN: C10.1, C12.1, C14.2, C15.2, CONLEFT.VMOT, D4.C, D7.A, IC1.3 (IN), IC2.3 (IN), JP11.4, R1.1, R2.1, SJ1.2, U$2.VMOT
VIN*: J5.8, JP21.4
VIN_: JP10.13

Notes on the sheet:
Battery connector
I2C battery voltage ADC
Programmable LEDs
Stepper motor drivers
Servo connectors
Voltage regulators
Buzzer
Joystick
Front
Left
Right
Additional connectors
OLED
Connection to microcontroller
Main board connection headers
Top board connection headers
Sensor module connector
Main board connector
Power-ON LED
Power-On LED
Switches
Analog input multiplexers
Sensors
Main board
Top boards
Sensor module

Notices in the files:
Eagle Files/V2.0/SteppyMk2_10x10.brd:
Licensed under MIT license
parts and their libraries:
SparkFun-Jumpers: Licensing: Creative Commons ShareAlike 4.0 International - https://creativecommons.org/licenses/by-sa/4.0
